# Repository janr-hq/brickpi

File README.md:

# brickpi

Open hardware Raspberry Pi controller for LEGO® MINDSTORMS® NXT/EV3 modular robots:
4 motor ports (with encoders), 4 sensor ports, own power supply. A from-scratch KiCad
re-implementation of the [BrickPi3](https://github.com/DexterInd/BrickPi3) by Dexter Industries
(MIT), developed as a bachelor's thesis project ("Sterownik z mikrokomputerem Raspberry Pi
dla robotów modułowych LEGO Mindstorms") and now continued as an open project.

> Polski skrót: sterownik dla robotów LEGO Mindstorms oparty na Raspberry Pi 3/4/5 – klon
> BrickPi3 (MIT). Repo zawiera projekt płytki (KiCad 8), opis protokołu SPI i zasilania,
> a w kolejnych etapach sterownik, firmware, obudowę i robota.

## Status

Version **0.1.0-dev** – repository bootstrap. Nothing here is a finished product yet.

| Area | State |
| --- | --- |
| Hardware (`hardware/`) | KiCad 8 project, REV2. A first board was fabricated (Dec 2024) and tested with motors, colour and distance sensors; the design was fixed afterwards (motor tracks, I2C level shifter, motor B/D power, inductor footprint) – the current revision is **not yet fabricated**. |
| Driver (`driver/`) | Planned. Today the original DexterInd Python driver works unchanged (spidev only). |
| Firmware (`firmware/`) | Planned. Today the original DexterInd binary v1.4.8 (ATSAMD21J18A) is flashed over SWD. |
| Enclosure (`enclosure/`) | FreeCAD case for board + Raspberry Pi 5 (prototype). |
| Simulation (`simulation/`) | Power-stage SPICE simulation (ngspice) available, see [docs/SIMULATION.md](docs/SIMULATION.md); protocol mock and robot simulation planned. |
| Robot (`robot/`) | Planned. |

## Raspberry Pi compatibility

| Board | Logic / SPI | Power from brickpi | Notes |
| --- | --- | --- | --- |
| Pi 3 B/B+ | ✅ | ✅ | Original BrickPi3 target. |
| Pi 4 B | ✅ | ✅ (≤ ~2 A) | |
| Pi 5 | ✅ (spidev) | ❌ | Needs 5 V / 5 A; the LM2576 + PTC stage is limited to ~2 A. See [docs/POWER.md](docs/POWER.md). Flashing over SWD needs the `rpi5.cfg` OpenOCD interface. |

The SPI protocol is documented in [docs/PROTOCOL.md](docs/PROTOCOL.md). Related open-source
projects and what we reuse: [docs/PRIOR-ART.md](docs/PRIOR-ART.md).

## Repository layout

| Path | Content |
| --- | --- |
| [`hardware/`](hardware/) | KiCad 8 schematic + PCB |
| [`docs/`](docs/) | Protocol, power analysis, design notes |
| [`driver/`](driver/) | Raspberry Pi driver (plan: Rust core + Python bindings) |
| [`firmware/`](firmware/) | MCU firmware (plan: Rust/Embassy, protocol-compatible) |
| [`enclosure/`](enclosure/) | Case (FreeCAD today, parametric later) |
| [`robot/`](robot/) | Reference robot built on the board |
| [`simulation/`](simulation/) | Board/robot simulation and protocol mock |

## Contributing

Branch from `develop`, open pull requests against `develop`, use
[Conventional Commits](https://www.conventionalcommits.org/) and add an entry to
[CHANGELOG.md](CHANGELOG.md). Details: [CLAUDE.md](CLAUDE.md).

## License and attribution

MIT – see [LICENSE](LICENSE). Based on BrickPi3 by Dexter Industries (MIT, © 2017 Dexter
Industries); see [NOTICE](NOTICE). This project is not affiliated with Dexter Industries or the
LEGO Group. LEGO® and MINDSTORMS® are trademarks of the LEGO Group.

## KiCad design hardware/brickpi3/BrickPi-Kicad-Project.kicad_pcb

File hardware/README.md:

# Hardware

KiCad 8 project of the board: `brickpi3/BrickPi-Kicad-Project.kicad_pro`.

Schematic sheets:

| Sheet | Content |
| --- | --- |
| `BrickPi-Kicad-Project.kicad_sch` | root: MCU ATSAMD21J18A, Raspberry Pi header, SWD, LEDs, I2C level shifter |
| `motors.kicad_sch` | 4 × motor port (TB6612 drivers, encoder inputs) |
| `sensors.kicad_sch` | 4 × sensor port (NXT/EV3, ADC, I2C, 9 V pin) |
| `power.kicad_sch` | battery input, LM2576 5 V buck, MIC5504 3V3, AP3012 9 V – see [docs/POWER.md](../docs/POWER.md) |

Board: 85.6 × 56.5 mm (Raspberry Pi HAT-like footprint), 2 layers. Board-specific design
rules are in `BrickPi-Kicad-Project.kicad_dru`.

## Revision history

| Date | Change |
| --- | --- |
| 2024-10 | REV2 drawn from the BrickPi3 v3.2.1 reference schematic (DexterInd). |
| 2024-12 | First board fabricated from this revision (tested: motors, colour and distance sensors). |
| 2025-02 | Fixed motor tracks. |
| 2025-04 | Updated I2C connections and motor B/D power lines; 100 µH inductor footprint changed to SDR1806. **Not fabricated yet.** |

## Libraries and 3D models

Symbols and footprints are embedded in the schematic/PCB files, so the project opens without
extra libraries. 3D models from third-party libraries (`${KICAD8_3RD_PARTY}/…`: RJ11
TJ6P6C, SS12D06, SK24A, 0ZCG0200FF2C, VLCF5020T, SBR10E45P5, Grove header) are **not**
included – the 3D view shows those parts without bodies.

## Fabrication files

Gerbers, drill files and BOM are not committed (they go stale). CI exports them from the
current PCB with `kicad-cli` and attaches them as a build artifact (`hardware-fab`).
Locally:

```sh
cd hardware/brickpi3
kicad-cli sch erc --severity-error -o erc.rpt BrickPi-Kicad-Project.kicad_sch
kicad-cli pcb drc --schematic-parity -o drc.rpt BrickPi-Kicad-Project.kicad_pcb
kicad-cli pcb export gerbers -o fab/ BrickPi-Kicad-Project.kicad_pcb
kicad-cli pcb export drill -o fab/ BrickPi-Kicad-Project.kicad_pcb
```

Interactive BOM: `ibom.config.ini` holds the settings for the
[InteractiveHtmlBom](https://github.com/openscopeproject/InteractiveHtmlBom) plugin.

## TODO

- Fix the ERC/DRC findings and make the CI check blocking.
- Silkscreen contains a university logo footprint (`PW:weiti`) – decide whether it stays in
  the public design.
- New power stage for Raspberry Pi 5 (see `docs/POWER.md`).
- Proper BOM with manufacturer part numbers.

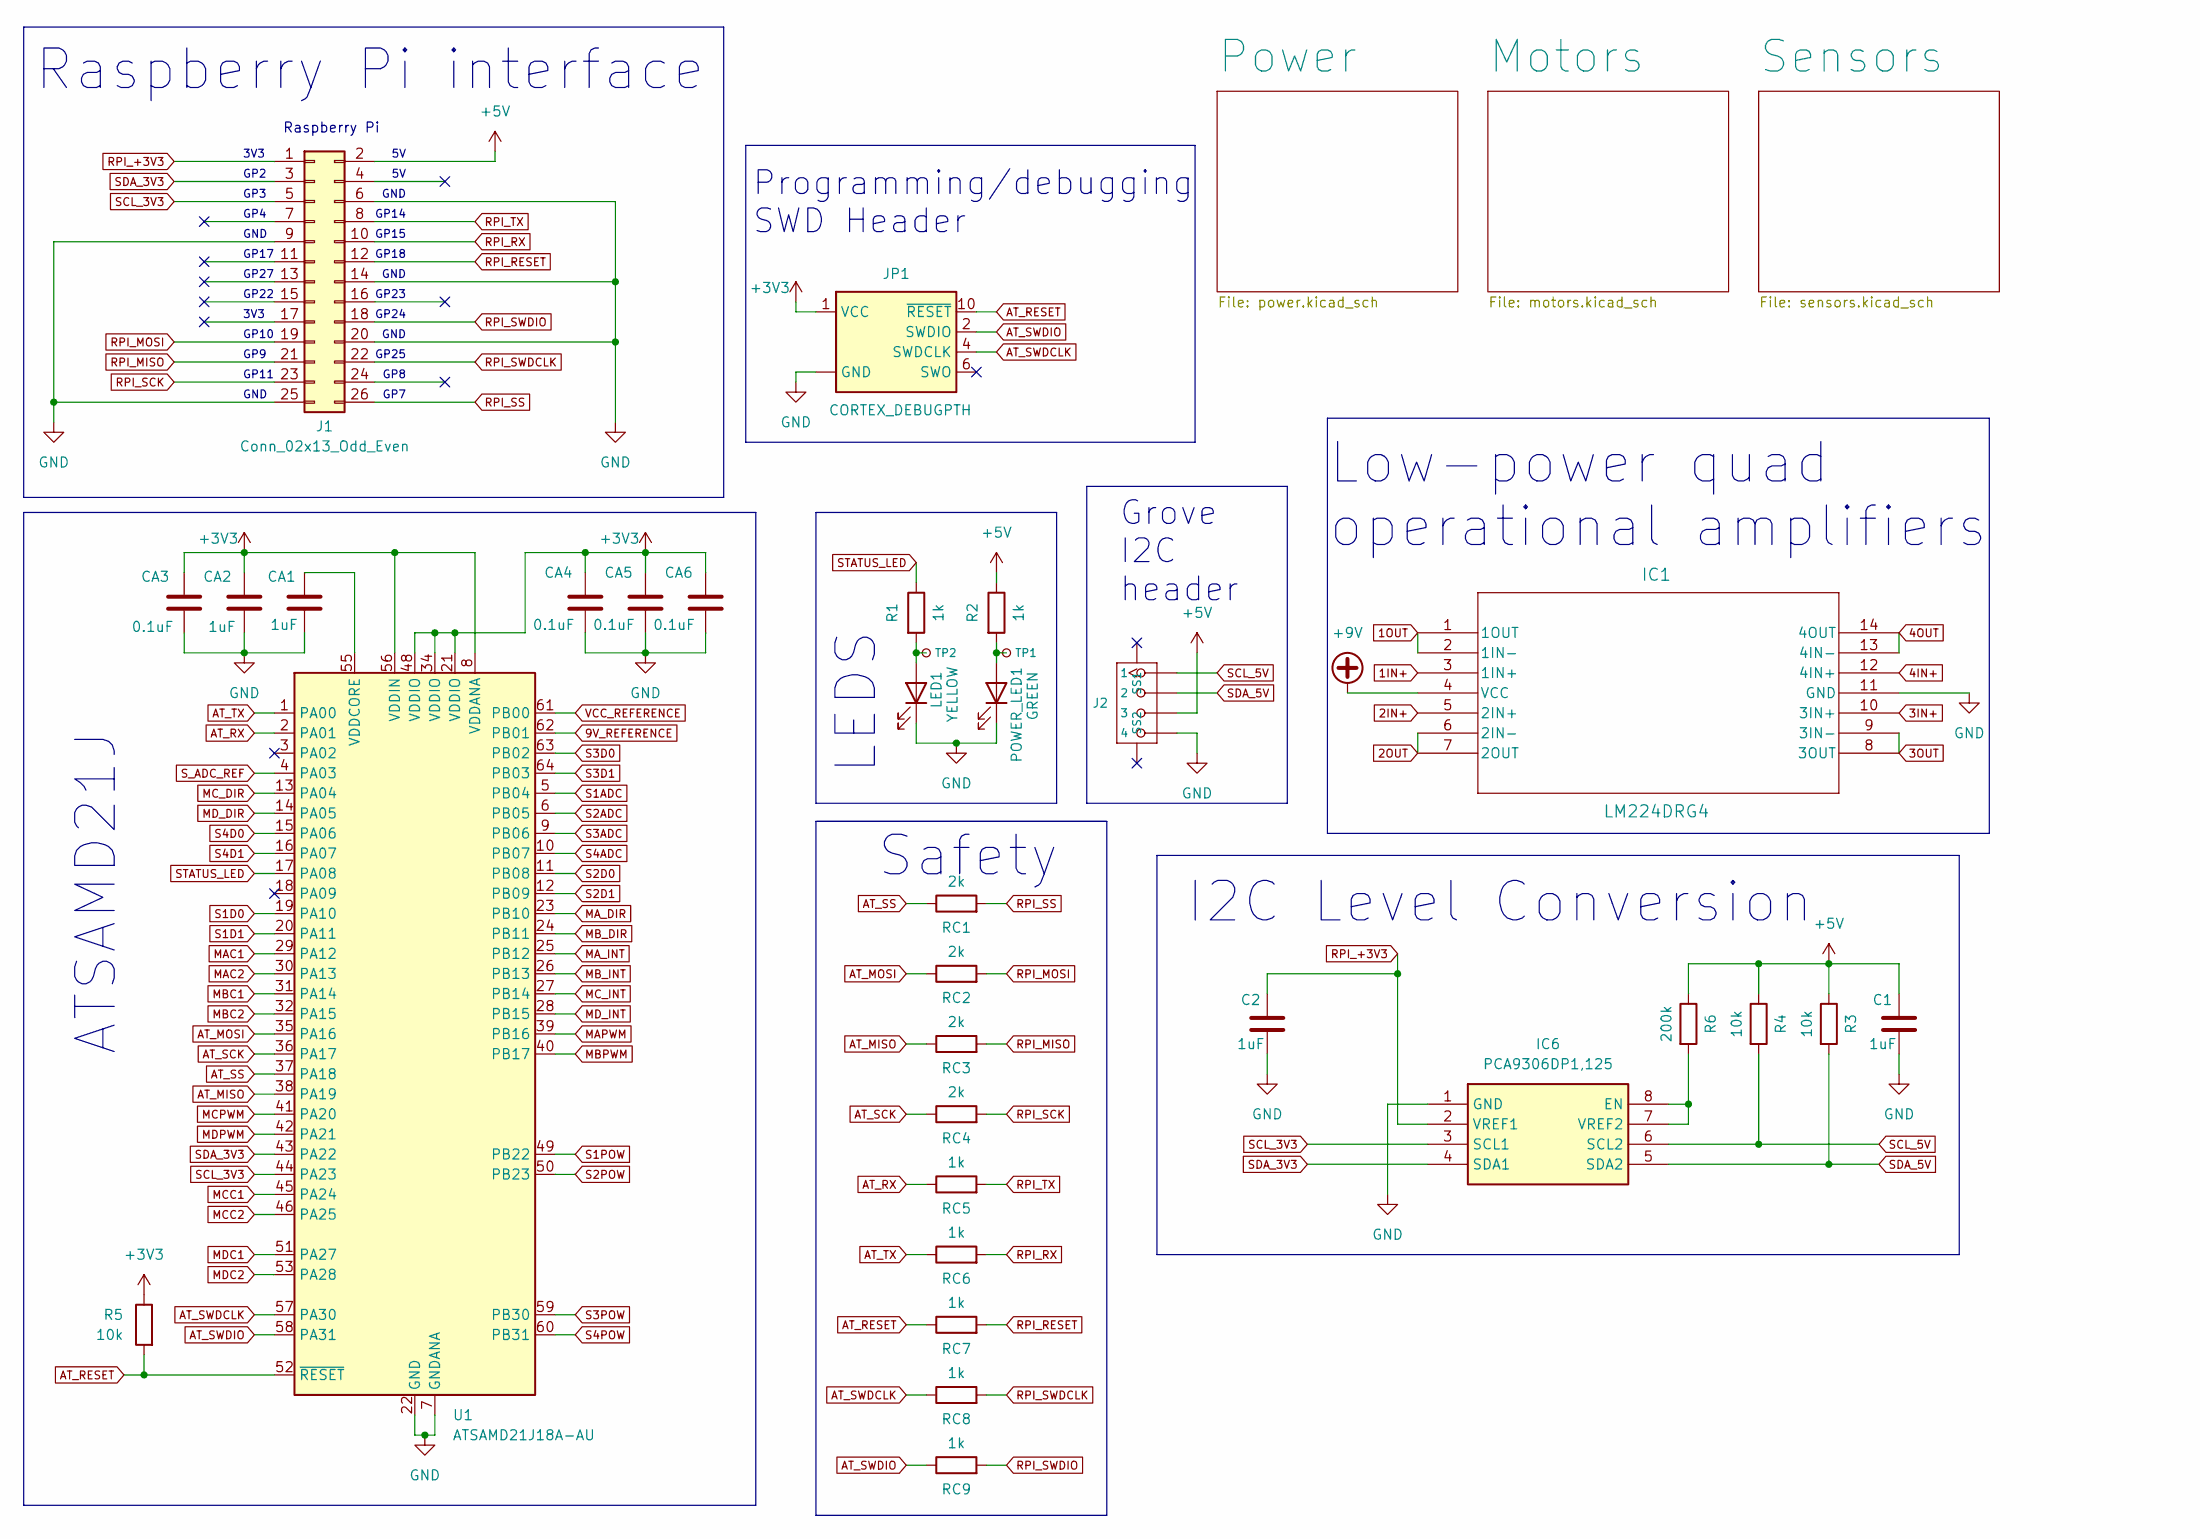
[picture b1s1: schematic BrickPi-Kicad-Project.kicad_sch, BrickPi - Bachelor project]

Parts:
C1, C2: 1uF; C_0603_1608Metric; Voltage 1kV; Tolerance 100%
CA1, CA2: 1uF; C_0603_1608Metric; Voltage 1kV; Tolerance 100%
CA3, CA4, CA5, CA6: 0.1uF; C_0603_1608Metric; Voltage 1kV; Tolerance 100%
IC1: LM224DRG4; SOIC-14_3.9x8.7mm_P1.27mm
IC6: PCA9306DP1,125; TSSOP-8_3x3mm_P0.65mm; Mouser Part Number 771-PCA9306DP1-G
J1: Conn_02x13_Odd_Even; PinHeader_2x13_P2.54mm_Vertical
J2: GROVE-CONNECTOR-SMD-90D_4+2P-2.0_; Grove Female Header - SMD-4P-2.0mm-90D
JP1: CORTEX_DEBUGPTH; PinHeader_2x05_P1.27mm_Vertical
LED1: YELLOW; LED_D5.0mm
POWER_LED1: GREEN; LED_D5.0mm
R1, R2: 1k; R_0603_1608Metric
R3, R4, R5: 10k; R_0603_1608Metric
R6: 200k; R_0603_1608Metric
RC1, RC2, RC3, RC4: 2k; R_0603_1608Metric
RC5, RC6, RC7, RC8, RC9: 1k; R_0603_1608Metric
TP1, TP2: TestPoint_Small; TestPoint_Pad_D1.0mm
U1: ATSAMD21J18A-AU; TQFP-64_10x10mm_P0.5mm

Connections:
1IN+: IC1.3 (1IN+); also elsewhere on the board
1OUT: IC1.1 (1OUT), IC1.2 (1IN-); also elsewhere on the board
2IN+: IC1.5 (2IN+); also elsewhere on the board
2OUT: IC1.6 (2IN-), IC1.7 (2OUT); also elsewhere on the board
3IN+: IC1.10 (3IN+); also elsewhere on the board
3OUT: IC1.8 (3OUT), IC1.9 (3IN-); also elsewhere on the board
4IN+: IC1.12 (4IN+); also elsewhere on the board
4OUT: IC1.13 (4IN-), IC1.14 (4OUT); also elsewhere on the board
9V_REFERENCE: U1.62 (PB01); also elsewhere on the board
+3V3: CA2.1, CA3.1, CA4.1, CA5.1, CA6.1, JP1.1 (VCC), R5.1, U1.8 (VDDANA), U1.21 (VDDIO), U1.34 (VDDIO), U1.48 (VDDIO), U1.56 (VDDIN); also elsewhere on the board
+5V: C1.1, J1.2, J2.3, R2.1, R3.1, R4.1, R6.1; also elsewhere on the board
+9V: IC1.4 (VCC); also elsewhere on the board
AT_MISO: RC3.1, U1.38 (PA19)
AT_MOSI: RC2.1, U1.35 (PA16)
AT_RESET: JP1.10 (~RESET), R5.2, RC7.1, U1.52 (~RESET)
AT_RX: RC5.1, U1.2 (PA01)
AT_SCK: RC4.1, U1.36 (PA17)
AT_SS: RC1.1, U1.37 (PA18)
AT_SWDCLK: JP1.4 (SWDCLK), RC8.1, U1.57 (PA30)
AT_SWDIO: JP1.2 (SWDIO), RC9.1, U1.58 (PA31)
AT_TX: RC6.1, U1.1 (PA00)
GND: C1.2, C2.2, CA1.2, CA2.2, CA3.2, CA4.2, CA5.2, CA6.2, IC1.11 (GND), IC6.1 (GND), J1.6, J1.9, J1.14, J1.20, J1.25, J2.4, JP1.3 (GND), JP1.5 (GND), JP1.9 (GND), LED1.1 (K), POWER_LED1.1 (K), U1.7 (GNDANA), U1.22 (GND), U1.33 (GND), U1.47 (GND), U1.54 (GND); also elsewhere on the board
MAC1: U1.29 (PA12); also elsewhere on the board
MAC2: U1.30 (PA13); also elsewhere on the board
MAPWM: U1.39 (PB16); also elsewhere on the board
MA_DIR: U1.23 (PB10); also elsewhere on the board
MA_INT: U1.25 (PB12); also elsewhere on the board
MBC1: U1.31 (PA14); also elsewhere on the board
MBC2: U1.32 (PA15); also elsewhere on the board
MBPWM: U1.40 (PB17); also elsewhere on the board
MB_DIR: U1.24 (PB11); also elsewhere on the board
MB_INT: U1.26 (PB13); also elsewhere on the board
MCC1: U1.45 (PA24); also elsewhere on the board
MCC2: U1.46 (PA25); also elsewhere on the board
MCPWM: U1.41 (PA20); also elsewhere on the board
MC_DIR: U1.13 (PA04); also elsewhere on the board
MC_INT: U1.27 (PB14); also elsewhere on the board
MDC1: U1.51 (PA27); also elsewhere on the board
MDC2: U1.53 (PA28); also elsewhere on the board
MDPWM: U1.42 (PA21); also elsewhere on the board
MD_DIR: U1.14 (PA05); also elsewhere on the board
MD_INT: U1.28 (PB15); also elsewhere on the board
unnamed: IC6.7 (VREF2), IC6.8 (EN), R6.2
unnamed: LED1.2 (A), R1.2, TP2.1
unnamed: POWER_LED1.2 (A), R2.2, TP1.1
unnamed: CA1.1, U1.55 (VDDCORE)
RPI_+3V3: C2.1, IC6.2 (VREF1), J1.1
RPI_MISO: J1.21, RC3.2
RPI_MOSI: J1.19, RC2.2
RPI_RESET: J1.12, RC7.2
RPI_RX: J1.10, RC6.2
RPI_SCK: J1.23, RC4.2
RPI_SS: J1.26, RC1.2
RPI_SWDCLK: J1.22, RC8.2
RPI_SWDIO: J1.18, RC9.2
RPI_TX: J1.8, RC5.2
S1ADC: U1.5 (PB04); also elsewhere on the board
S1D0: U1.19 (PA10); also elsewhere on the board
S1D1: U1.20 (PA11); also elsewhere on the board
S1POW: U1.49 (PB22); also elsewhere on the board
S2ADC: U1.6 (PB05); also elsewhere on the board
S2D0: U1.11 (PB08); also elsewhere on the board
S2D1: U1.12 (PB09); also elsewhere on the board
S2POW: U1.50 (PB23); also elsewhere on the board
S3ADC: U1.9 (PB06); also elsewhere on the board
S3D0: U1.63 (PB02); also elsewhere on the board
S3D1: U1.64 (PB03); also elsewhere on the board
S3POW: U1.59 (PB30); also elsewhere on the board
S4ADC: U1.10 (PB07); also elsewhere on the board
S4D0: U1.15 (PA06); also elsewhere on the board
S4D1: U1.16 (PA07); also elsewhere on the board
S4POW: U1.60 (PB31); also elsewhere on the board
SCL_3V3: IC6.3 (SCL1), J1.5, U1.44 (PA23)
SCL_5V: IC6.6 (SCL2), J2.1, R4.2
SDA_3V3: IC6.4 (SDA1), J1.3, U1.43 (PA22)
SDA_5V: IC6.5 (SDA2), J2.2, R3.2
STATUS_LED: R1.1, U1.17 (PA08)
S_ADC_REF: U1.4 (PA03); also elsewhere on the board
VCC_REFERENCE: U1.61 (PB00); also elsewhere on the board

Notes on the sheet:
GND
GP22
LEDS
GP7
GP8
3V3
GP14
GP15
I2C Level Conversion
GP23
GP3
Low-power quad operational amplifiers
GP9
Raspberry Pi
Raspberry Pi interface
GP10
GP11
Programming/debugging SWD Header
GP18
Safety
GP27
GP24
GP4
GP25
ATSAMD21J
Grove I2C header
GP2
GP17

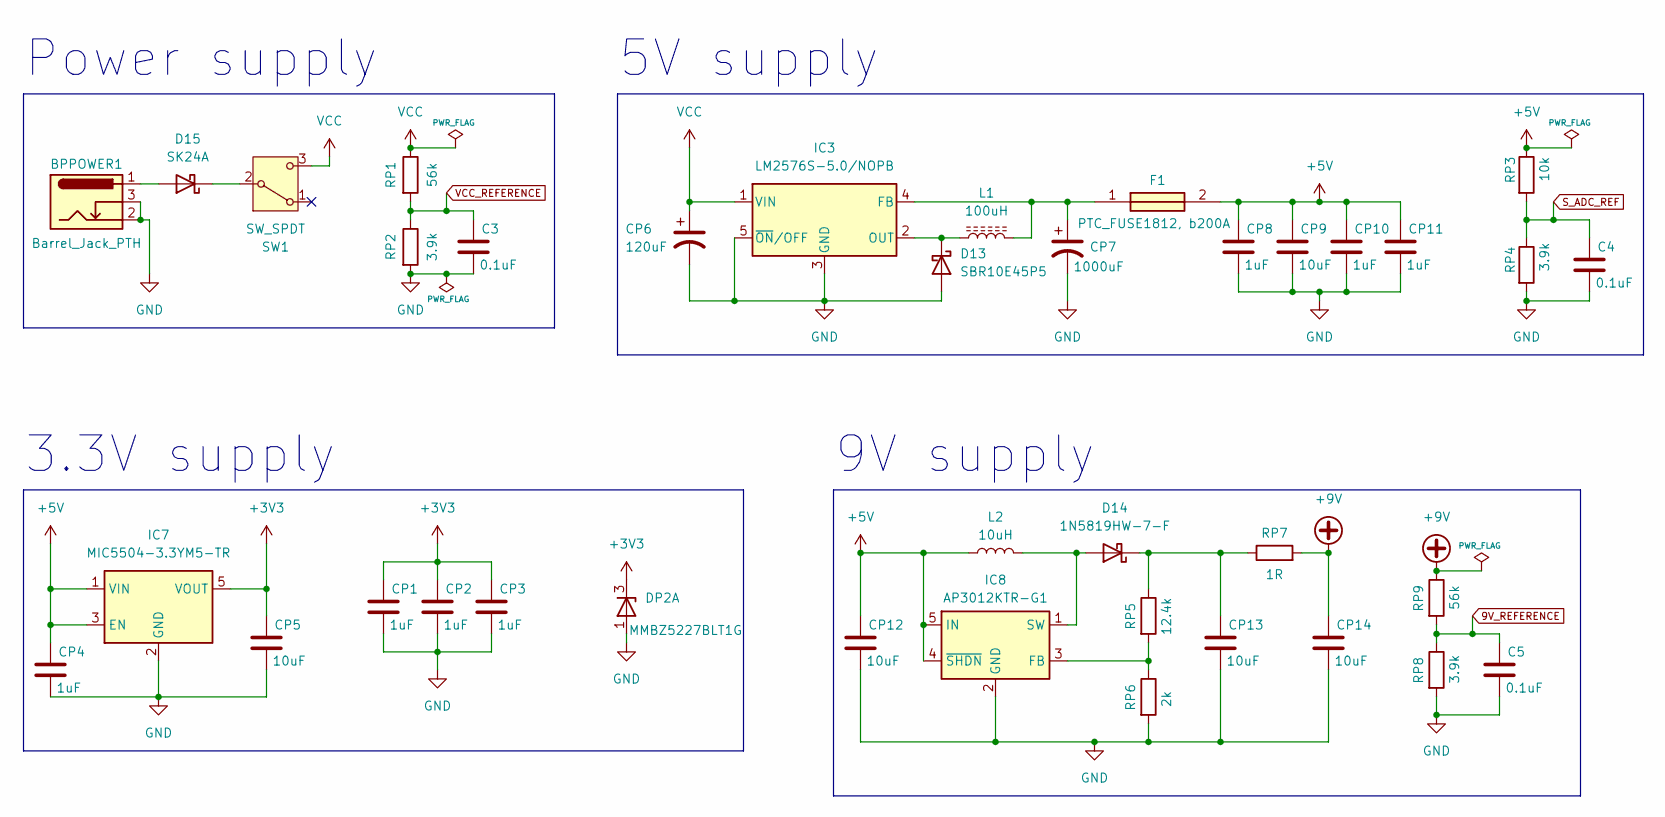
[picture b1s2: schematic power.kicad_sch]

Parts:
BPPOWER1: Barrel_Jack_PTH; BarrelJack_Horizontal
C3, C4, C5: 0.1uF; C_0603_1608Metric; Voltage 1kV; Tolerance 100%
CP1, CP2, CP3, CP4, CP8, CP10, CP11: 1uF; C_0603_1608Metric; Voltage 1kV; Tolerance 100%
CP5, CP9, CP12, CP13, CP14: 10uF; C_0805_2012Metric; Voltage 1kV; Tolerance 100%
CP6: 120uF; C_Radial_D6.3mm_H11.0mm_P2.50mm
CP7: 1000uF; C_Radial_D10.0mm_H12.5mm_P5.00mm
D13: SBR10E45P5; D_PowerDI-5
D14: 1N5819HW-7-F; D_SOD-123
D15: SK24A; DO-214AA
DP2: MMBZ5227BLT1G; SOT-23-3
F1: PTC_FUSE1812, b200A; FUSC4632X120N; Manufacturer_Part_Number 0ZCG0200FF2C
IC3: LM2576S-5.0/NOPB; TO-263-5_TabPin3
IC7: MIC5504-3.3YM5-TR; SOT-23-5
IC8: AP3012KTR-G1; SOT-23-5
L1: 100uH; L_Bourns_SDR1806
L2: 10uH; VLCF5020
RP1, RP9: 56k; R_0603_1608Metric
RP2, RP4, RP8: 3.9k; R_0603_1608Metric
RP3: 10k; R_0603_1608Metric
RP5: 12.4k; R_0603_1608Metric
RP6: 2k; R_0603_1608Metric
RP7: 1R; R_0603_1608Metric
SW1: SW_SPDT; SLW12764663ARAND

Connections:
9V_REFERENCE: C5.1, RP8.1, RP9.2; also elsewhere on the board
+3V3: CP1.1, CP2.1, CP3.1, CP5.1, DP2.3 (K), IC7.5 (VOUT); also elsewhere on the board
+5V: CP4.1, CP8.1, CP9.1, CP10.1, CP11.1, CP12.1, F1.2, IC7.1 (VIN), IC7.3 (EN), IC8.4 (~SHDN), IC8.5 (IN), L2.1, RP3.1; also elsewhere on the board
+9V: CP14.1, RP7.2, RP9.1; also elsewhere on the board
GND: BPPOWER1.2 (GND), BPPOWER1.3 (GNDBREAK), C3.2, C4.2, C5.2, CP1.2, CP2.2, CP3.2, CP4.2, CP5.2, CP6.2, CP7.2, CP8.2, CP9.2, CP10.2, CP11.2, CP12.2, CP13.2, CP14.2, D13.2 (A), DP2.1 (A), IC3.3 (GND), IC3.5 (~ON/OFF), IC7.2 (GND), IC8.2 (GND), RP2.2, RP4.2, RP6.2, RP8.2; also elsewhere on the board
unnamed: BPPOWER1.1 (PWR), D15.2 (A)
unnamed: D13.1 (K), IC3.2 (OUT), L1.1
unnamed: D14.2 (A), IC8.1 (SW), L2.2
unnamed: CP13.1, D14.1 (K), RP5.1, RP7.1
unnamed: D15.1 (K), SW1.2 (B)
unnamed: CP7.1, F1.1, IC3.4 (FB), L1.2
unnamed: IC8.3 (FB), RP5.2, RP6.1
S_ADC_REF: C4.1, RP3.2, RP4.1; also elsewhere on the board
VCC: CP6.1, IC3.1 (VIN), RP1.1, SW1.3 (C); also elsewhere on the board
VCC_REFERENCE: C3.1, RP1.2, RP2.1; also elsewhere on the board

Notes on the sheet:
3.3V supply
Power supply
9V supply
5V supply

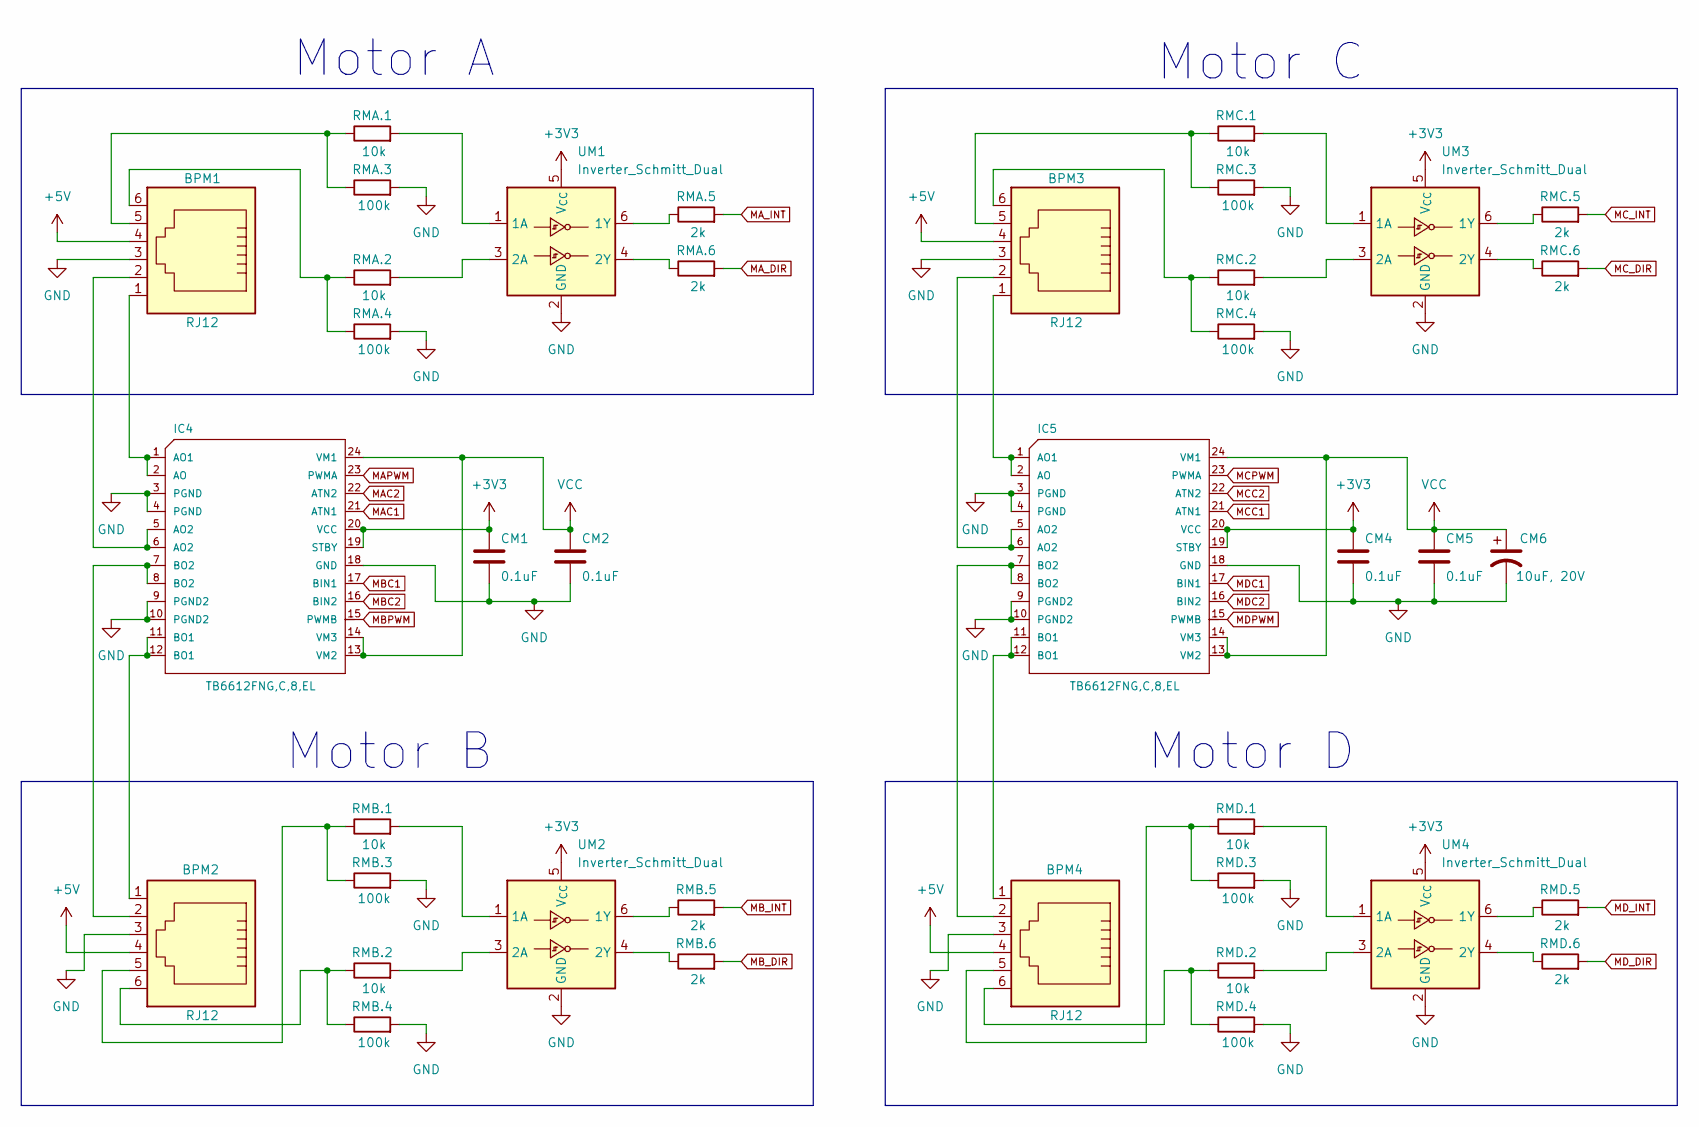
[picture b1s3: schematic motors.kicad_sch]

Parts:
BPM1, BPM2, BPM3, BPM4: RJ12; RJ25-15x12mm
CM1, CM2, CM4, CM5: 0.1uF; C_0603_1608Metric; Voltage 1kV; Tolerance 100%
CM6: 10uF, 20V; CP_EIA-3528-21_Kemet-B
IC4, IC5: TB6612FNG,C,8,EL; SSOP-24_5.3x8.2mm_P0.65mm; MPN TB6612FNG-O_C8_EL
RMA.1, RMA.2: 10k; R_0603_1608Metric
RMA.3, RMA.4: 100k; R_0603_1608Metric
RMA.5, RMA.6: 2k; R_0603_1608Metric
RMB.1, RMB.2: 10k; R_0603_1608Metric
RMB.3, RMB.4: 100k; R_0603_1608Metric
RMB.5, RMB.6: 2k; R_0603_1608Metric
RMC.1, RMC.2: 10k; R_0603_1608Metric
RMC.3, RMC.4: 100k; R_0603_1608Metric
RMC.5, RMC.6: 2k; R_0603_1608Metric
RMD.1, RMD.2: 10k; R_0603_1608Metric
RMD.3, RMD.4: 100k; R_0603_1608Metric
RMD.5, RMD.6: 2k; R_0603_1608Metric
UM1, UM2, UM3, UM4: Inverter_Schmitt_Dual; SOT-363_SC-70-6

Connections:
+3V3: CM1.1, CM4.1, IC4.19 (STBY), IC4.20 (VCC), IC5.19 (STBY), IC5.20 (VCC), UM1.5 (V_{CC}), UM2.5 (V_{CC}), UM3.5 (V_{CC}), UM4.5 (V_{CC}); also elsewhere on the board
+5V: BPM1.4, BPM2.4, BPM3.4, BPM4.4; also elsewhere on the board
GND: BPM1.3, BPM2.3, BPM3.3, BPM4.3, CM1.2, CM2.2, CM4.2, CM5.2, CM6.2, IC4.3 (PGND), IC4.4 (PGND), IC4.9 (PGND2), IC4.10 (PGND2), IC4.18 (GND), IC5.3 (PGND), IC5.4 (PGND), IC5.9 (PGND2), IC5.10 (PGND2), IC5.18 (GND), RMA.3.2, RMA.4.2, RMB.3.2, RMB.4.2, RMC.3.2, RMC.4.2, RMD.3.2, RMD.4.2, UM1.2 (GND), UM2.2 (GND), UM3.2 (GND), UM4.2 (GND); also elsewhere on the board
MAC1: IC4.21 (ATN1); also elsewhere on the board
MAC2: IC4.22 (ATN2); also elsewhere on the board
MAPWM: IC4.23 (PWMA); also elsewhere on the board
MA_DIR: RMA.6.2; also elsewhere on the board
MA_INT: RMA.5.2; also elsewhere on the board
MBC1: IC4.17 (BIN1); also elsewhere on the board
MBC2: IC4.16 (BIN2); also elsewhere on the board
MBPWM: IC4.15 (PWMB); also elsewhere on the board
MB_DIR: RMB.6.2; also elsewhere on the board
MB_INT: RMB.5.2; also elsewhere on the board
MCC1: IC5.21 (ATN1); also elsewhere on the board
MCC2: IC5.22 (ATN2); also elsewhere on the board
MCPWM: IC5.23 (PWMA); also elsewhere on the board
MC_DIR: RMC.6.2; also elsewhere on the board
MC_INT: RMC.5.2; also elsewhere on the board
MDC1: IC5.17 (BIN1); also elsewhere on the board
MDC2: IC5.16 (BIN2); also elsewhere on the board
MDPWM: IC5.15 (PWMB); also elsewhere on the board
MD_DIR: RMD.6.2; also elsewhere on the board
MD_INT: RMD.5.2; also elsewhere on the board
unnamed: BPM1.2, IC4.5 (AO2), IC4.6 (AO2)
unnamed: BPM1.5, RMA.1.1, RMA.3.1
unnamed: BPM1.6, RMA.2.1, RMA.4.1
unnamed: BPM2.1, IC4.11 (BO1), IC4.12 (BO1)
unnamed: BPM2.2, IC4.7 (BO2), IC4.8 (BO2)
unnamed: BPM2.5, RMB.1.1, RMB.3.1
unnamed: BPM2.6, RMB.2.1, RMB.4.1
unnamed: BPM3.2, IC5.5 (AO2), IC5.6 (AO2)
unnamed: BPM3.5, RMC.1.1, RMC.3.1
unnamed: BPM3.6, RMC.2.1, RMC.4.1
unnamed: BPM4.1, IC5.11 (BO1), IC5.12 (BO1)
unnamed: BPM4.2, IC5.7 (BO2), IC5.8 (BO2)
unnamed: BPM4.5, RMD.1.1, RMD.3.1
unnamed: BPM4.6, RMD.2.1, RMD.4.1
unnamed: BPM1.1, IC4.1 (AO1), IC4.2 (AO)
unnamed: BPM3.1, IC5.1 (AO1), IC5.2 (AO)
unnamed: RMA.1.2, UM1.1 (1A)
unnamed: RMA.5.1, UM1.6 (1Y)
unnamed: RMA.2.2, UM1.3 (2A)
unnamed: RMA.6.1, UM1.4 (2Y)
unnamed: RMB.1.2, UM2.1 (1A)
unnamed: RMB.5.1, UM2.6 (1Y)
unnamed: RMB.2.2, UM2.3 (2A)
unnamed: RMB.6.1, UM2.4 (2Y)
unnamed: RMC.1.2, UM3.1 (1A)
unnamed: RMC.5.1, UM3.6 (1Y)
unnamed: RMC.2.2, UM3.3 (2A)
unnamed: RMC.6.1, UM3.4 (2Y)
unnamed: RMD.1.2, UM4.1 (1A)
unnamed: RMD.5.1, UM4.6 (1Y)
unnamed: RMD.2.2, UM4.3 (2A)
unnamed: RMD.6.1, UM4.4 (2Y)
VCC: CM2.1, CM5.1, CM6.1, IC4.13 (VM2), IC4.14 (VM3), IC4.24 (VM1), IC5.13 (VM2), IC5.14 (VM3), IC5.24 (VM1); also elsewhere on the board

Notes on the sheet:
Motor D
Motor A
Motor B
Motor C

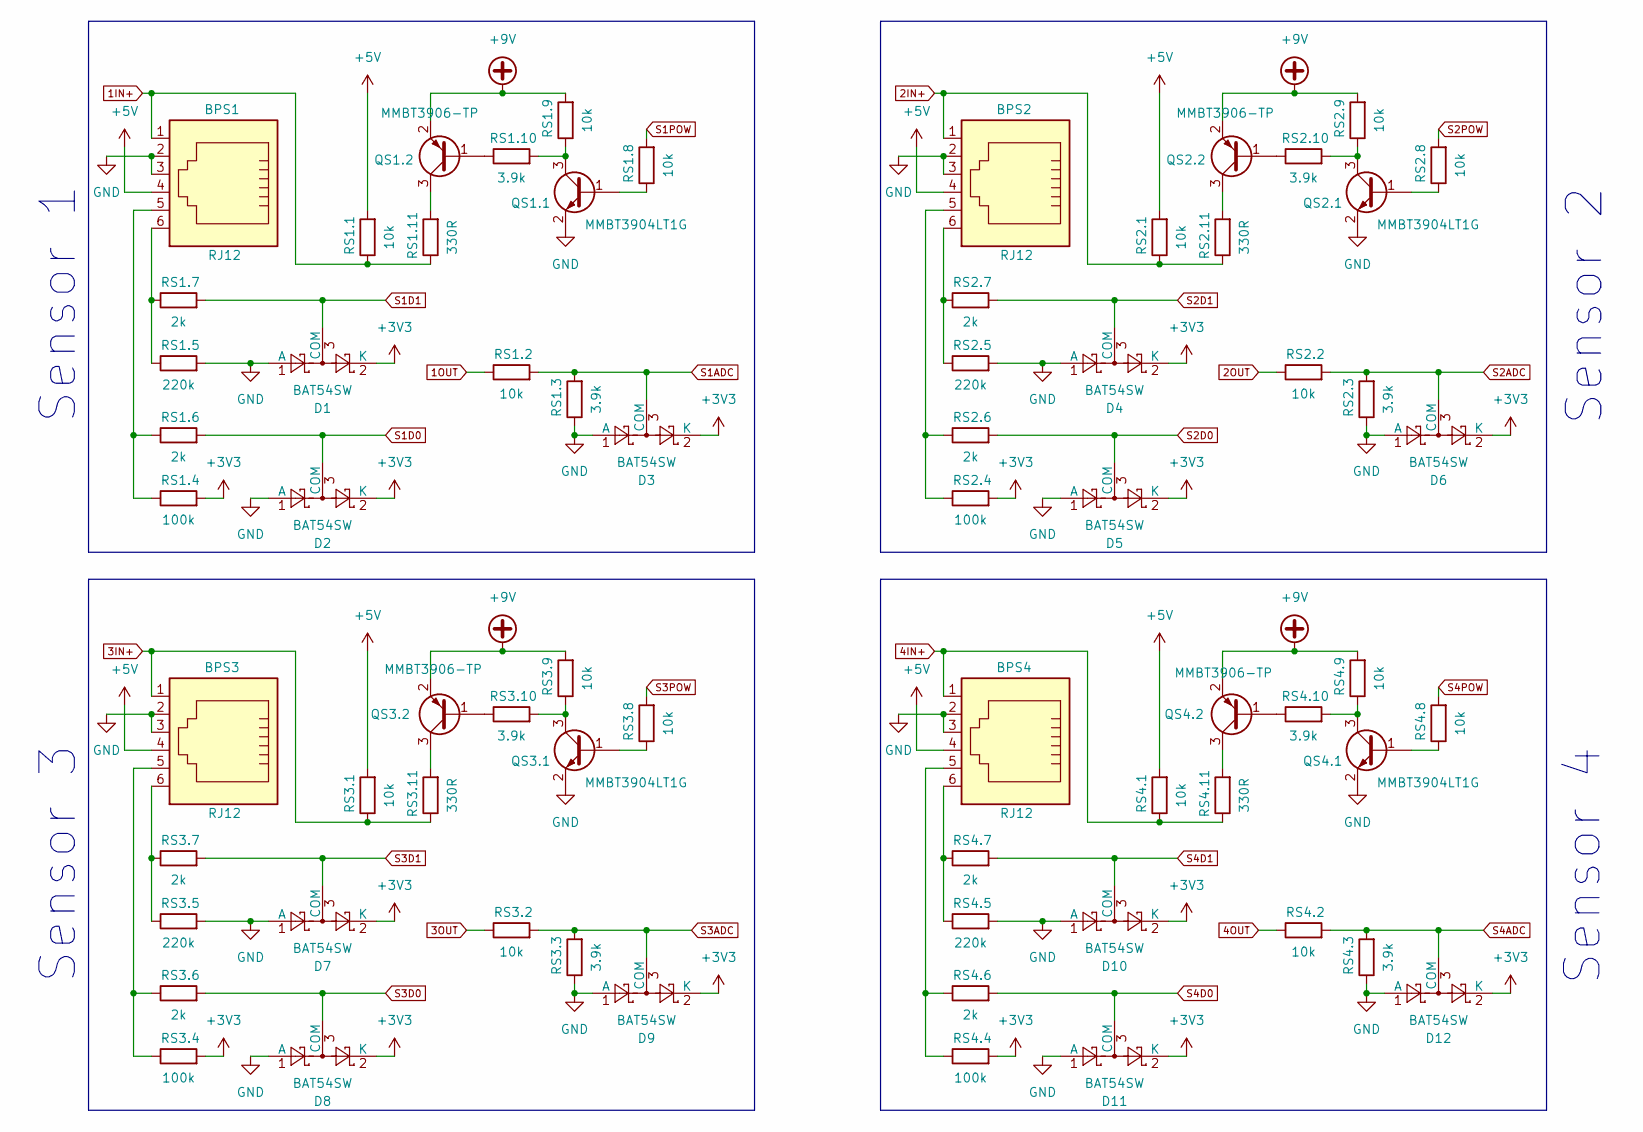
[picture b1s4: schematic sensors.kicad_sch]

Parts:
BPS1, BPS2, BPS3, BPS4: RJ12; RJ25-15x12mm
D1, D2, D3, D4, D5, D6, D7, D8, D9, D10, D11, D12: BAT54SW; SOT-23
QS1.1, QS2.1, QS3.1, QS4.1: MMBT3904LT1G; SOT-23-3
QS1.2, QS2.2, QS3.2, QS4.2: MMBT3906-TP; SOT-23-3
RS1.1, RS1.2, RS1.8, RS1.9, RS2.1, RS2.2, RS2.8, RS2.9, RS3.1, RS3.2, RS3.8, RS3.9, RS4.1, RS4.2, RS4.8, RS4.9: 10k; R_0603_1608Metric
RS1.3, RS1.10, RS2.3, RS2.10, RS3.3, RS3.10, RS4.3, RS4.10: 3.9k; R_0603_1608Metric
RS1.4, RS2.4, RS3.4, RS4.4: 100k; R_0603_1608Metric
RS1.5, RS2.5, RS3.5, RS4.5: 220k; R_0603_1608Metric
RS1.6, RS1.7, RS2.6, RS2.7, RS3.6, RS3.7, RS4.6, RS4.7: 2k; R_0603_1608Metric
RS1.11, RS2.11, RS3.11, RS4.11: 330R; R_0603_1608Metric

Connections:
1IN+: BPS1.1, RS1.1.1, RS1.11.1; also elsewhere on the board
1OUT: RS1.2.1; also elsewhere on the board
2IN+: BPS2.1, RS2.1.1, RS2.11.1; also elsewhere on the board
2OUT: RS2.2.1; also elsewhere on the board
3IN+: BPS3.1, RS3.1.1, RS3.11.1; also elsewhere on the board
3OUT: RS3.2.1; also elsewhere on the board
4IN+: BPS4.1, RS4.1.1, RS4.11.1; also elsewhere on the board
4OUT: RS4.2.1; also elsewhere on the board
+3V3: D1.2 (K), D2.2 (K), D3.2 (K), D4.2 (K), D5.2 (K), D6.2 (K), D7.2 (K), D8.2 (K), D9.2 (K), D10.2 (K), D11.2 (K), D12.2 (K), RS1.4.2, RS2.4.2, RS3.4.2, RS4.4.2; also elsewhere on the board
+5V: BPS1.4, BPS2.4, BPS3.4, BPS4.4, RS1.1.2, RS2.1.2, RS3.1.2, RS4.1.2; also elsewhere on the board
+9V: QS1.2.2 (E), QS2.2.2 (E), QS3.2.2 (E), QS4.2.2 (E), RS1.9.2, RS2.9.2, RS3.9.2, RS4.9.2; also elsewhere on the board
GND: BPS1.2, BPS1.3, BPS2.2, BPS2.3, BPS3.2, BPS3.3, BPS4.2, BPS4.3, D1.1 (A), D2.1 (A), D3.1 (A), D4.1 (A), D5.1 (A), D6.1 (A), D7.1 (A), D8.1 (A), D9.1 (A), D10.1 (A), D11.1 (A), D12.1 (A), QS1.1.2 (E), QS2.1.2 (E), QS3.1.2 (E), QS4.1.2 (E), RS1.3.1, RS1.5.2, RS2.3.1, RS2.5.2, RS3.3.1, RS3.5.2, RS4.3.1, RS4.5.2; also elsewhere on the board
unnamed: BPS1.5, RS1.4.1, RS1.6.1
unnamed: BPS1.6, RS1.5.1, RS1.7.1
unnamed: BPS2.5, RS2.4.1, RS2.6.1
unnamed: BPS2.6, RS2.5.1, RS2.7.1
unnamed: BPS3.5, RS3.4.1, RS3.6.1
unnamed: BPS3.6, RS3.5.1, RS3.7.1
unnamed: BPS4.5, RS4.4.1, RS4.6.1
unnamed: BPS4.6, RS4.5.1, RS4.7.1
unnamed: QS1.1.1 (B), RS1.8.1
unnamed: QS1.1.3 (C), RS1.9.1, RS1.10.2
unnamed: QS1.2.1 (B), RS1.10.1
unnamed: QS1.2.3 (C), RS1.11.2
unnamed: QS2.1.1 (B), RS2.8.1
unnamed: QS2.1.3 (C), RS2.9.1, RS2.10.2
unnamed: QS2.2.1 (B), RS2.10.1
unnamed: QS2.2.3 (C), RS2.11.2
unnamed: QS3.1.1 (B), RS3.8.1
unnamed: QS3.1.3 (C), RS3.9.1, RS3.10.2
unnamed: QS3.2.1 (B), RS3.10.1
unnamed: QS3.2.3 (C), RS3.11.2
unnamed: QS4.1.1 (B), RS4.8.1
unnamed: QS4.1.3 (C), RS4.9.1, RS4.10.2
unnamed: QS4.2.1 (B), RS4.10.1
unnamed: QS4.2.3 (C), RS4.11.2
S1ADC: D3.3 (COM), RS1.2.2, RS1.3.2; also elsewhere on the board
S1D0: D2.3 (COM), RS1.6.2; also elsewhere on the board
S1D1: D1.3 (COM), RS1.7.2; also elsewhere on the board
S1POW: RS1.8.2; also elsewhere on the board
S2ADC: D6.3 (COM), RS2.2.2, RS2.3.2; also elsewhere on the board
S2D0: D5.3 (COM), RS2.6.2; also elsewhere on the board
S2D1: D4.3 (COM), RS2.7.2; also elsewhere on the board
S2POW: RS2.8.2; also elsewhere on the board
S3ADC: D9.3 (COM), RS3.2.2, RS3.3.2; also elsewhere on the board
S3D0: D8.3 (COM), RS3.6.2; also elsewhere on the board
S3D1: D7.3 (COM), RS3.7.2; also elsewhere on the board
S3POW: RS3.8.2; also elsewhere on the board
S4ADC: D12.3 (COM), RS4.2.2, RS4.3.2; also elsewhere on the board
S4D0: D11.3 (COM), RS4.6.2; also elsewhere on the board
S4D1: D10.3 (COM), RS4.7.2; also elsewhere on the board
S4POW: RS4.8.2; also elsewhere on the board

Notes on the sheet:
Sensor 2
Sensor 4
Sensor 3
Sensor 1

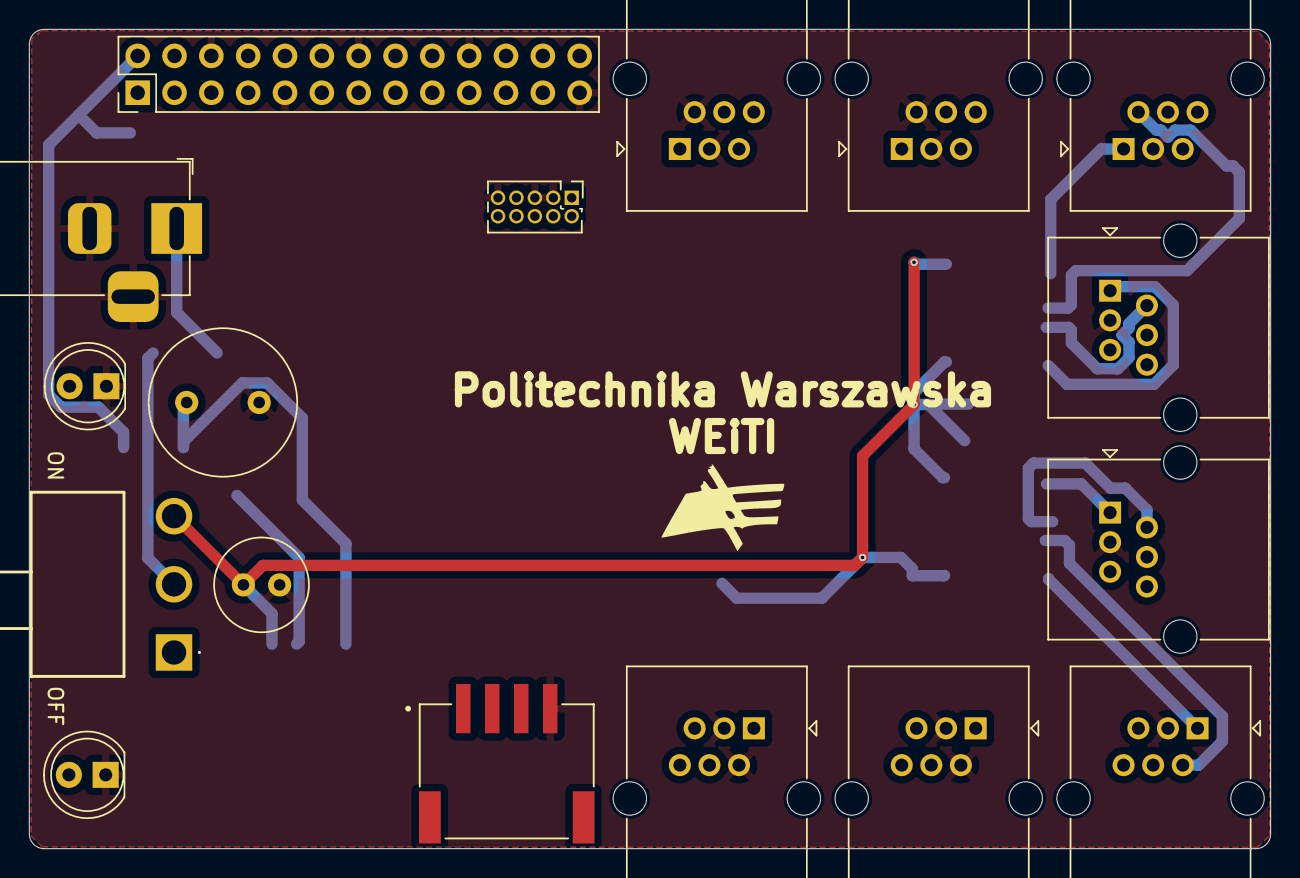
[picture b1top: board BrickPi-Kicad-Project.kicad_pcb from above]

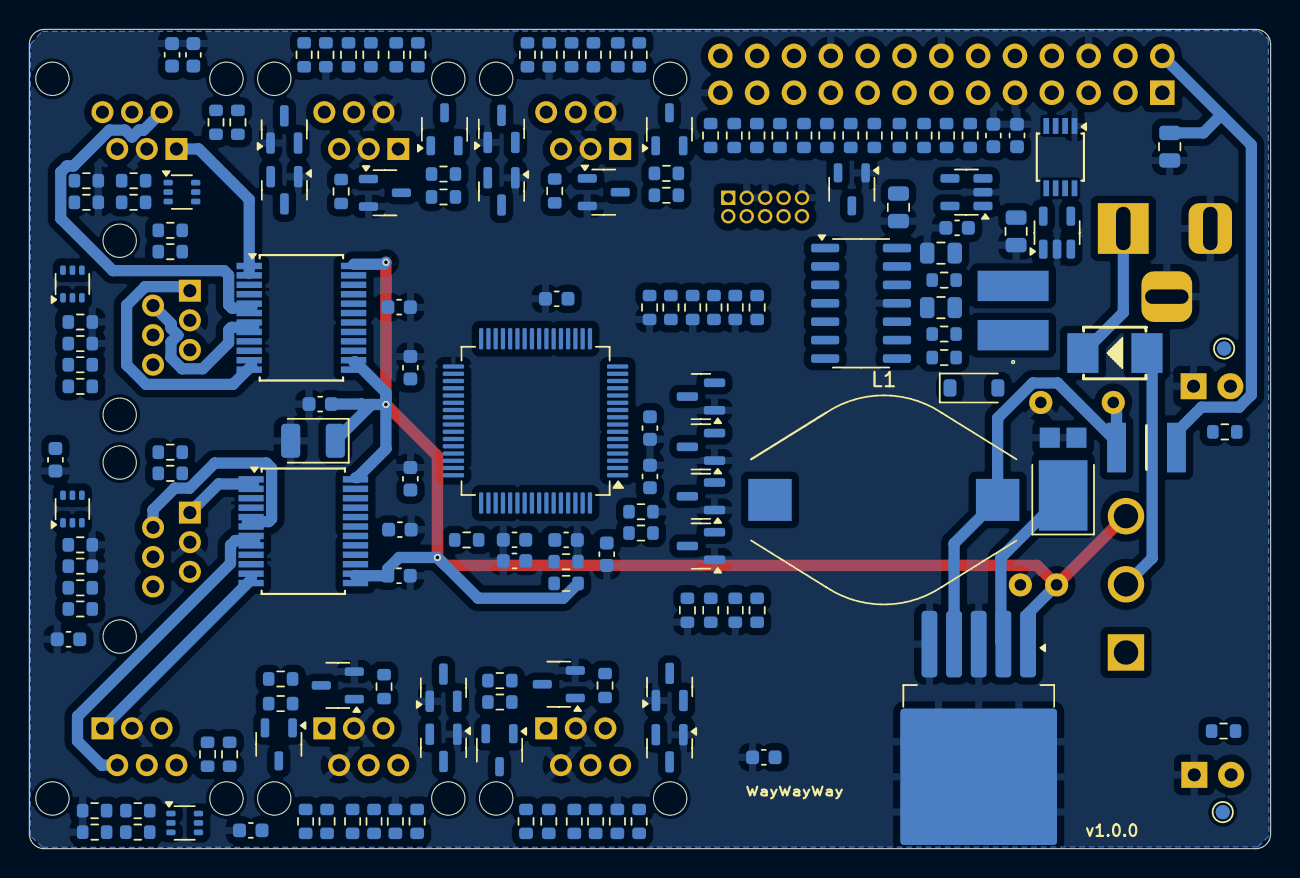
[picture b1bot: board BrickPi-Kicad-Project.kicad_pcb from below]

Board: 2 copper layers, 85.6 x 56.5 mm, 178 parts (161 on the bottom side), 143 nets.
